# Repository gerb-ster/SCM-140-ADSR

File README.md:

# SCM 140 ADSR

This module is a straight up clone of the ADSR module found it the famous Roland System-100m modular synthesizer from the ’70’s. It consists of 2 identical ADSR generators with a positive and a negative output. I’ve build this some years ago, there are other simpler designs out there, however, it was a really good learning experience.

## Status: Finished

- done: first schematic & board design
- done: breadboard and test
- done: design frontpanel
- done: order PCB and build prototype

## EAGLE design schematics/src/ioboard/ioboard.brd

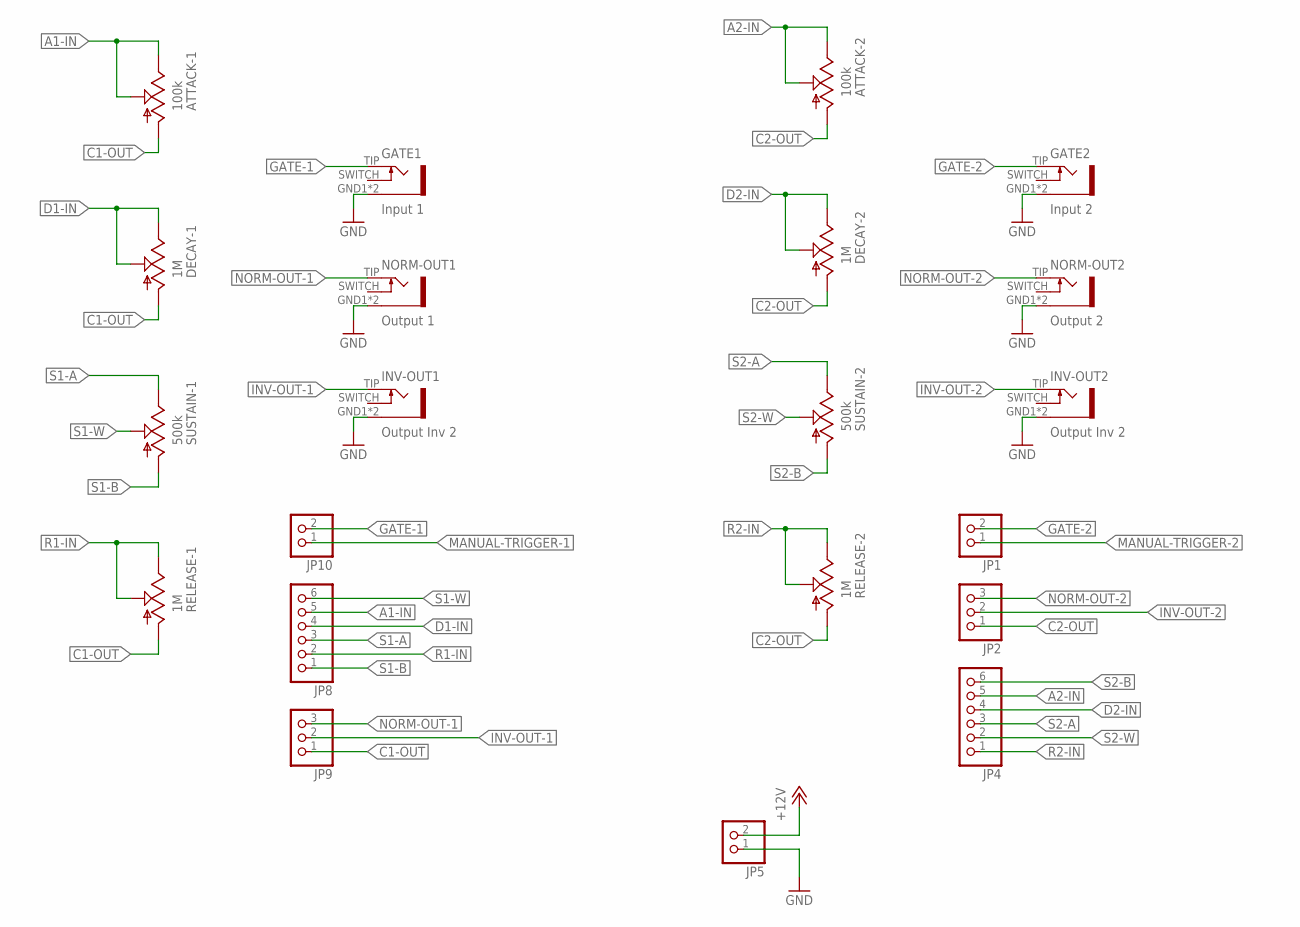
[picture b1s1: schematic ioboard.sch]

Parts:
ATTACK-1, ATTACK-2: 100k; EVUF
DECAY-1, DECAY-2: 1M; EVUF
GATE1: Input 1; PJ301BM
GATE2: Input 2; PJ301BM
INV-OUT1, INV-OUT2: Output Inv 2; PJ301BM
JP1, JP5, JP10: PINHD-1X2; 1X02
JP2, JP9: PINHD-1X3; 1X03
JP4, JP8: PINHD-1X6; 1X06
NORM-OUT1: Output 1; PJ301BM
NORM-OUT2: Output 2; PJ301BM
RELEASE-1, RELEASE-2: 1M; EVUF
SUSTAIN-1, SUSTAIN-2: 500k; EVUF

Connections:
+12V: JP5.2
A1-IN: ATTACK-1.2 (S), ATTACK-1.3 (E), JP8.5
A2-IN: ATTACK-2.2 (S), ATTACK-2.3 (E), JP4.5
C1-OUT: ATTACK-1.1 (A), DECAY-1.1 (A), JP9.1, RELEASE-1.1 (A)
C2-OUT: ATTACK-2.1 (A), DECAY-2.1 (A), JP2.1, RELEASE-2.1 (A)
D1-IN: DECAY-1.2 (S), DECAY-1.3 (E), JP8.4
D2-IN: DECAY-2.2 (S), DECAY-2.3 (E), JP4.4
GATE-1: GATE1.TIP (3), JP10.2
GATE-2: GATE2.TIP (3), JP1.2
GND: GATE1.GND1 (5), GATE1.GND2 (5), GATE2.GND1 (5), GATE2.GND2 (5), INV-OUT1.GND1 (5), INV-OUT1.GND2 (5), INV-OUT2.GND1 (5), INV-OUT2.GND2 (5), JP5.1, NORM-OUT1.GND1 (5), NORM-OUT1.GND2 (5), NORM-OUT2.GND1 (5), NORM-OUT2.GND2 (5)
INV-OUT-1: INV-OUT1.TIP (3), JP9.2
INV-OUT-2: INV-OUT2.TIP (3), JP2.2
MANUAL-TRIGGER-1: JP10.1
MANUAL-TRIGGER-2: JP1.1
NORM-OUT-1: JP9.3, NORM-OUT1.TIP (3)
NORM-OUT-2: JP2.3, NORM-OUT2.TIP (3)
R1-IN: JP8.2, RELEASE-1.2 (S), RELEASE-1.3 (E)
R2-IN: JP4.1, RELEASE-2.2 (S), RELEASE-2.3 (E)
S1-A: JP8.3, SUSTAIN-1.3 (E)
S1-B: JP8.1, SUSTAIN-1.1 (A)
S1-W: JP8.6, SUSTAIN-1.2 (S)
S2-A: JP4.3, SUSTAIN-2.3 (E)
S2-B: JP4.6, SUSTAIN-2.1 (A)
S2-W: JP4.2, SUSTAIN-2.2 (S)

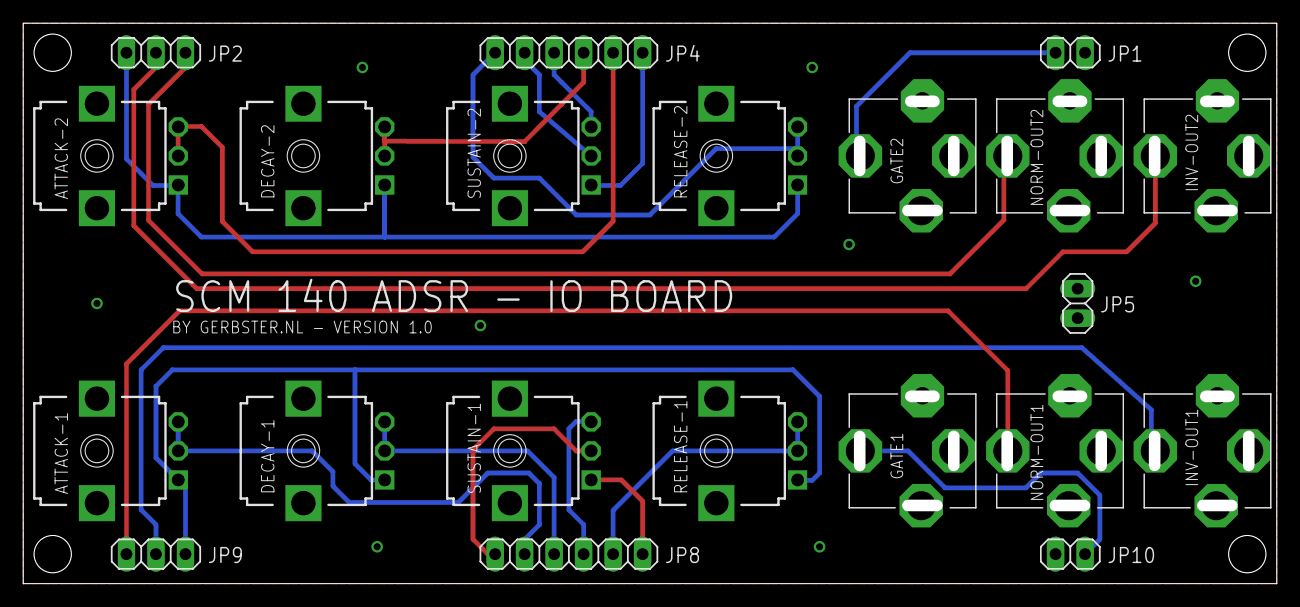
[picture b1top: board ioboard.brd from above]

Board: 2 copper layers, 107.0 x 47.3 mm, 21 parts (0 on the bottom side), 21 nets.

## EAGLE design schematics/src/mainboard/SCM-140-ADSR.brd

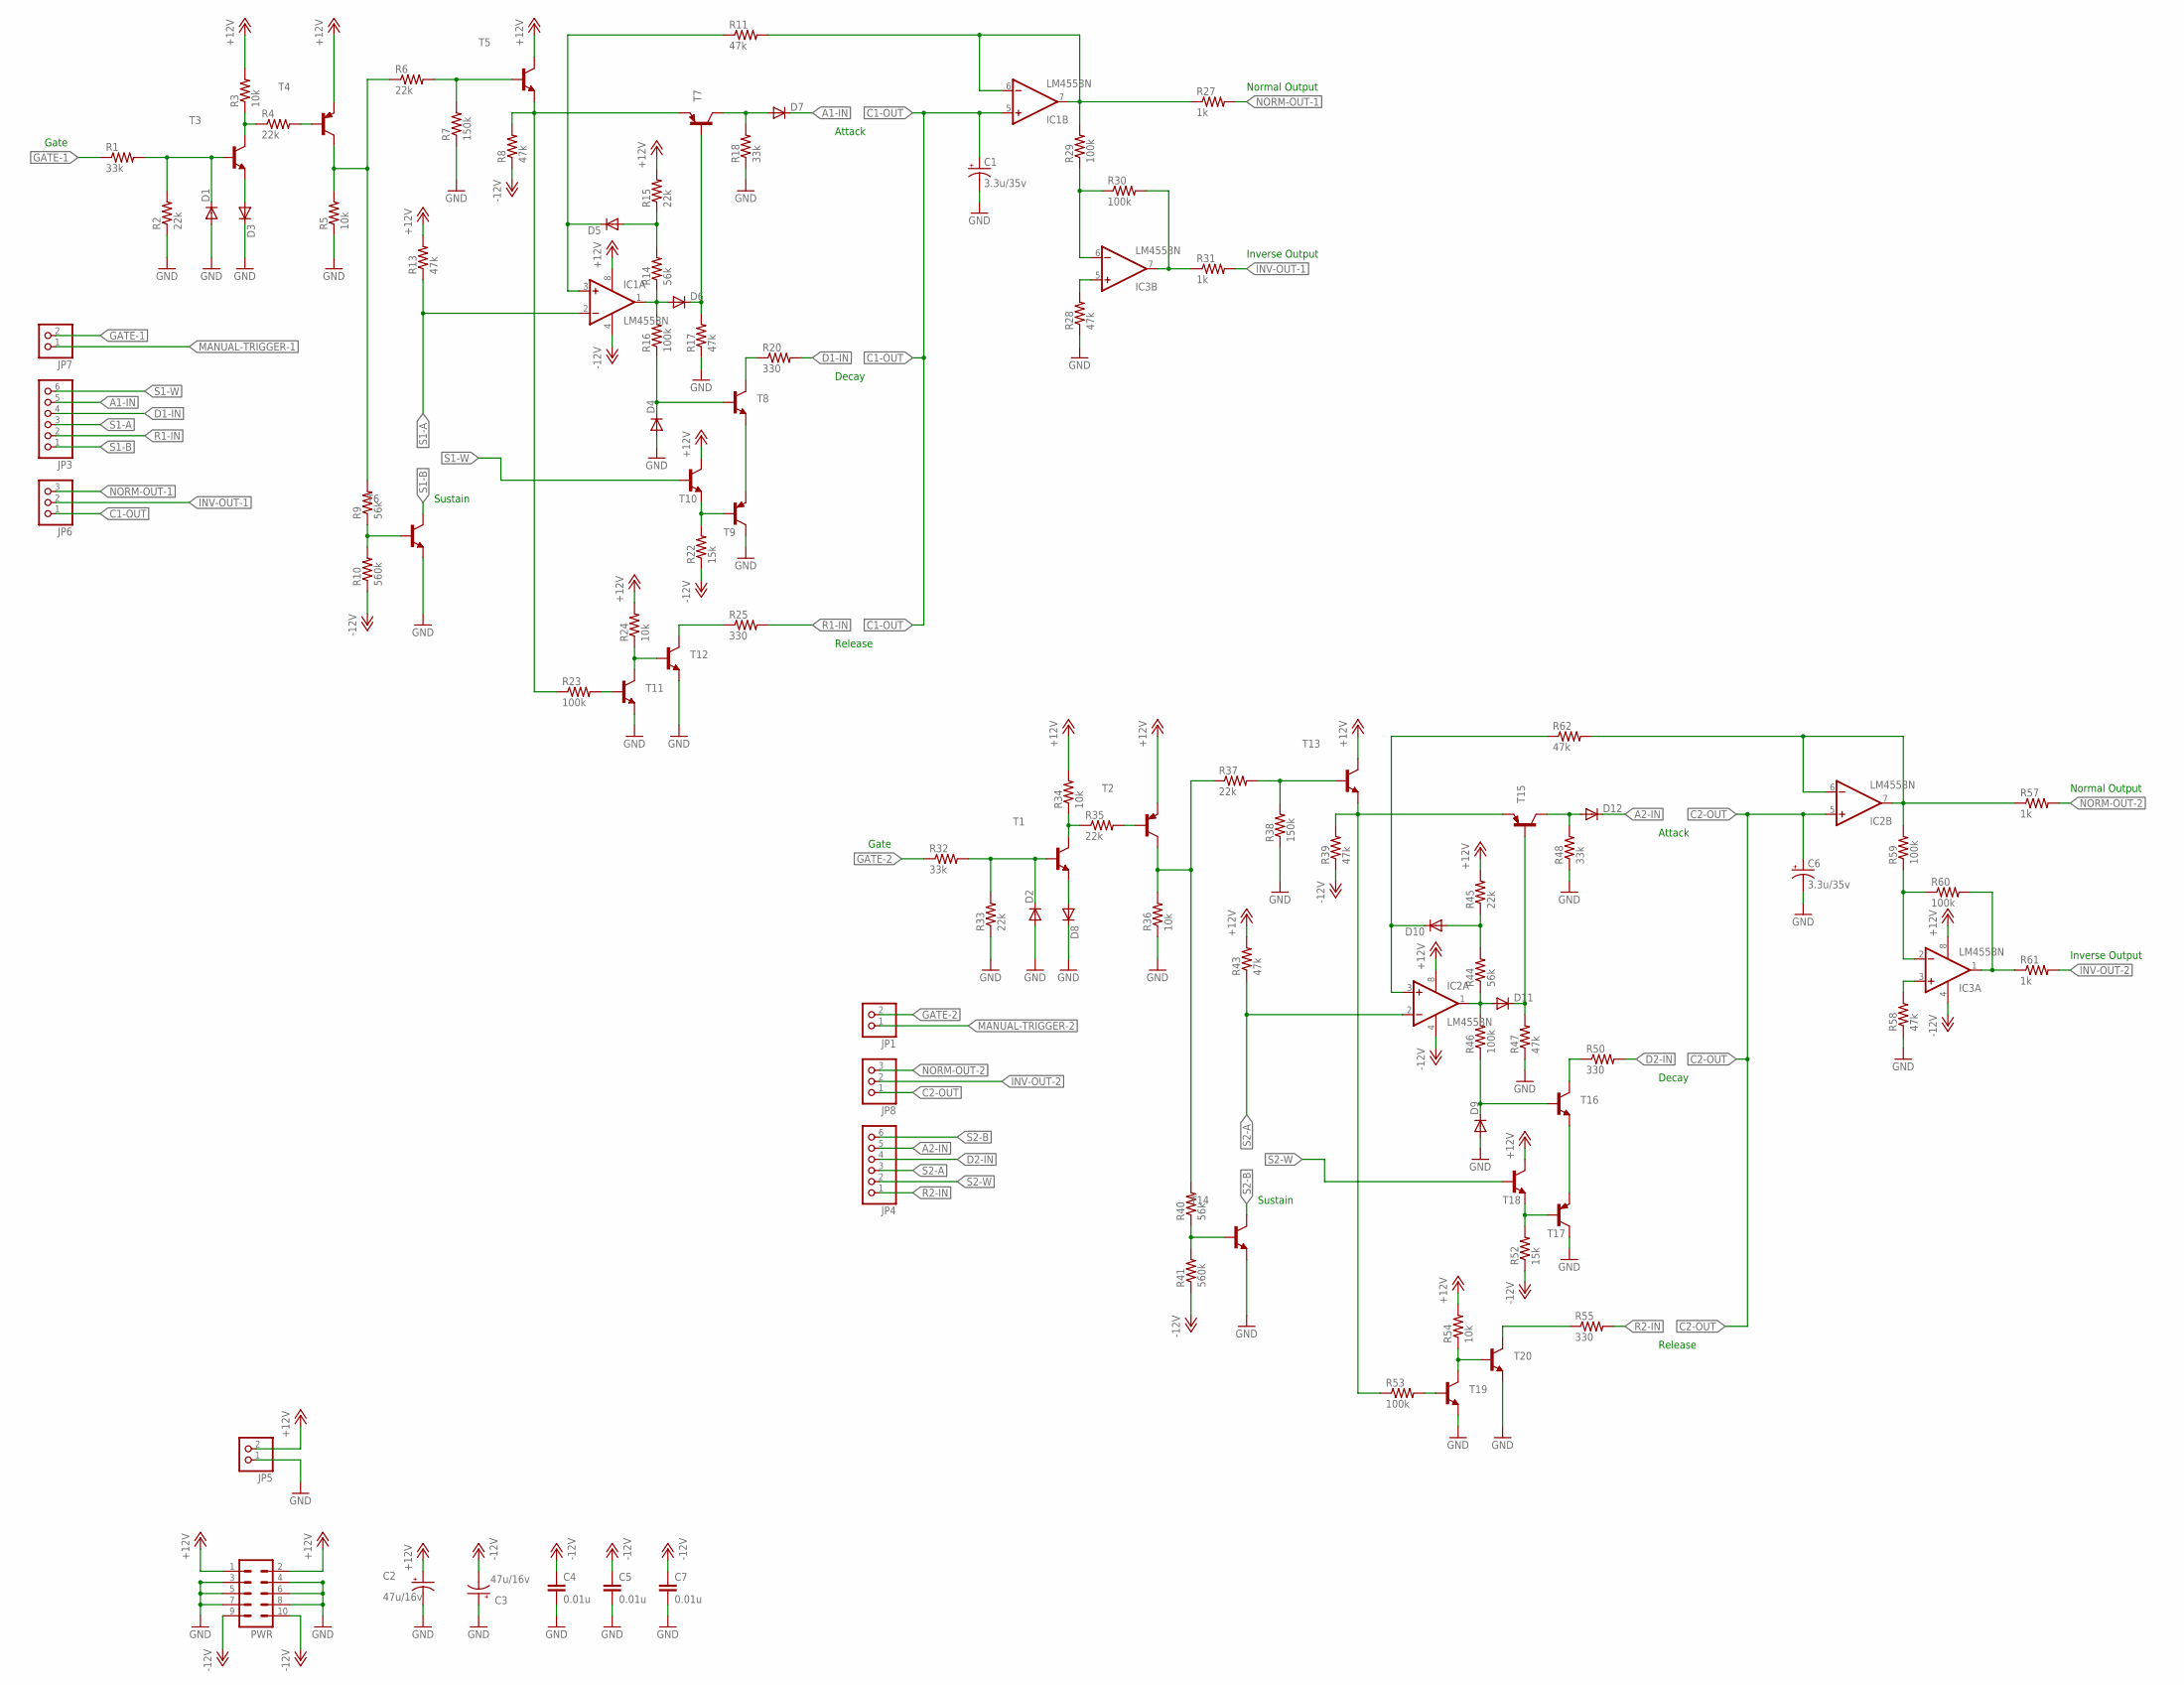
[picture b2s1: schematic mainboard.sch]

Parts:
C1, C6: 3.3u/35v; E2,5-5
C2, C3: 47u/16v; E2,5-5
C4, C5, C7: 0.01u; C025-024X044
D1, D2, D3, D4, D5, D6, D7, D8, D9, D10, D11, D12: 1N4148DO35-7; DO35-7
IC1, IC2, IC3: LM4558N; DIL08
JP1, JP5, JP7: PINHD-1X2; 1X02
JP3, JP4: PINHD-1X6; 1X06
JP6, JP8: PINHD-1X3; 1X03
PWR: ML10
R1, R18, R32, R48: 33k; 0204/7
R2, R4, R6, R15, R33, R35, R37, R45: 22k; 0204/7
R3, R5, R24, R34, R36, R54: 10k; 0204/7
R7, R38: 150k; 0204/7
R8, R11, R13, R17, R28, R39, R43, R47, R58, R62: 47k; 0204/7
R9, R14, R40, R44: 56k; 0204/7
R10, R41: 560k; 0204/7
R16, R23, R29, R30, R46, R53, R59, R60: 100k; 0204/7
R20, R25, R50, R55: 330; 0204/7
R22, R52: 15k; 0204/7
R27, R31, R57, R61: 1k; 0204/7
T1, T3, T5, T6, T8, T10, T11, T12, T13, T14, T16, T18, T19, T20: BC547B-NPN-TO92-CBE; TO92-CBE
T2, T4, T7, T9, T15, T17: BC557B-PNP-TO92-EBC; TO92-EBC

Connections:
+12V: C2.+, IC1.8 (V+), IC2.8 (V+), IC3.8 (V+), JP5.2, PWR.1, PWR.2, R3.2, R13.2, R15.2, R24.2, R34.2, R43.2, R45.2, R54.2, T2.E, T4.E, T5.C, T10.C, T13.C, T18.C
-12V: C3.-, C4.1, C5.1, C7.1, IC1.4 (V-), IC2.4 (V-), IC3.4 (V-), PWR.9, PWR.10, R8.1, R10.1, R22.1, R39.1, R41.1, R52.1
A1-IN: D7.C, JP3.5
A2-IN: D12.C, JP4.5
C1-OUT: C1.+, IC1.5 (+IN), JP6.1
C2-OUT: C6.+, IC2.5 (+IN), JP8.1
D1-IN: JP3.4, R20.2
D2-IN: JP4.4, R50.2
GATE-1: JP7.2, R1.1
GATE-2: JP1.2, R32.1
GND: C1.-, C2.-, C3.+, C4.2, C5.2, C6.-, C7.2, D1.A, D2.A, D3.C, D4.A, D8.C, D9.A, JP5.1, PWR.3, PWR.4, PWR.5, PWR.6, PWR.7, PWR.8, R2.1, R5.1, R7.1, R17.1, R18.1, R28.1, R33.1, R36.1, R38.1, R47.1, R48.1, R58.1, T6.E, T9.C, T11.E, T12.E, T14.E, T17.C, T19.E, T20.E
INV-OUT-1: JP6.2, R31.2
INV-OUT-2: JP8.2, R61.2
MANUAL-TRIGGER-1: D1.C, JP7.1, R1.2, R2.2, T3.B
MANUAL-TRIGGER-2: D2.C, JP1.1, R32.2, R33.2, T1.B
unnamed: D5.C, IC1.3 (+IN), R11.1
unnamed: D3.A, T3.E
unnamed: R3.1, R4.1, T3.C
unnamed: R4.2, T4.B
unnamed: R5.2, R6.1, R9.2, T4.C
unnamed: R8.2, R23.1, T5.E, T7.E
unnamed: R6.2, R7.2, T5.B
unnamed: R9.1, R10.2, T6.B
unnamed: D6.A, IC1.1 (OUT), R14.1, R16.2
unnamed: D4.C, R16.1, T8.B
unnamed: D5.A, R14.2, R15.1
unnamed: IC1.6 (-IN), IC1.7 (OUT), R11.2, R27.1, R29.2
unnamed: D7.A, R18.2, T7.C
unnamed: D6.C, R17.2, T7.B
unnamed: IC3.6 (-IN), R29.1, R30.1
unnamed: R20.1, T8.C
unnamed: R22.2, T9.B, T10.E
unnamed: T8.E, T9.E
unnamed: R23.2, T11.B
unnamed: R24.1, T11.C, T12.B
unnamed: R25.1, T12.C
unnamed: IC3.7 (OUT), R30.2, R31.1
unnamed: D8.A, T1.E
unnamed: IC3.5 (+IN), R28.2
unnamed: R34.1, R35.1, T1.C
unnamed: R35.2, T2.B
unnamed: R36.2, R37.1, R40.2, T2.C
unnamed: R39.2, R53.1, T13.E, T15.E
unnamed: R37.2, R38.2, T13.B
unnamed: R40.1, R41.2, T14.B
unnamed: D11.A, IC2.1 (OUT), R44.1, R46.2
unnamed: D9.C, R46.1, T16.B
unnamed: D10.A, R44.2, R45.1
unnamed: IC2.6 (-IN), IC2.7 (OUT), R57.1, R59.2, R62.2
unnamed: D11.C, R47.2, T15.B
unnamed: D12.A, R48.2, T15.C
unnamed: R50.1, T16.C
unnamed: R52.2, T17.B, T18.E
unnamed: T16.E, T17.E
unnamed: R53.2, T19.B
unnamed: R54.1, T19.C, T20.B
unnamed: R55.1, T20.C
unnamed: IC3.2 (-IN), R59.1, R60.1
unnamed: IC3.1 (OUT), R60.2, R61.1
unnamed: IC3.3 (+IN), R58.2
unnamed: D10.C, IC2.3 (+IN), R62.1
NORM-OUT-1: JP6.3, R27.2
NORM-OUT-2: JP8.3, R57.2
R1-IN: JP3.2, R25.2
R2-IN: JP4.1, R55.2
S1-A: IC1.2 (-IN), JP3.3, R13.1
S1-B: JP3.1, T6.C
S1-W: JP3.6, T10.B
S2-A: IC2.2 (-IN), JP4.3, R43.1
S2-B: JP4.6, T14.C
S2-W: JP4.2, T18.B

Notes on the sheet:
Attack
Decay
Release
Sustain
Gate
Normal Output
Inverse Output

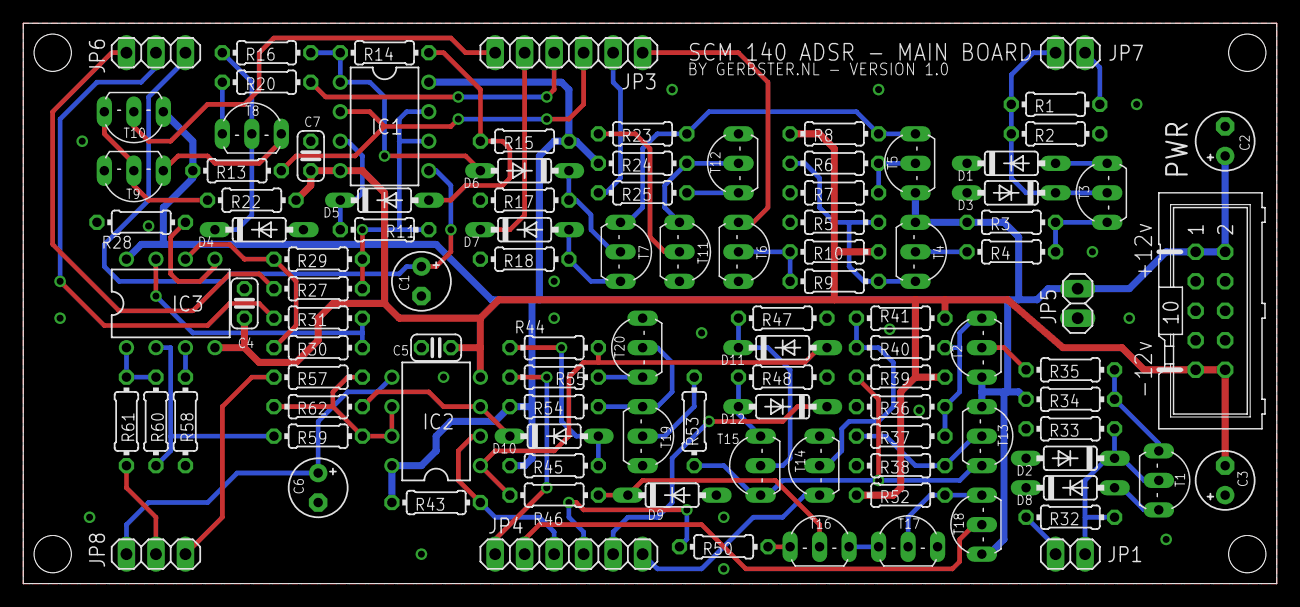
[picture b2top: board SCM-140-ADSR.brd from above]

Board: 2 copper layers, 108.0 x 48.3 mm, 104 parts (0 on the bottom side), 71 nets.

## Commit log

2021-05-06 some files
2021-05-07 Added files & structure
2021-05-10 Added Status
2021-05-11 Added Status & Images
2021-08-06 Updated some schematics and docs
2021-08-10 Fixed some bugs and updated documentation
2022-04-20 Some updates & bugfixes
2022-04-22 Fixed schematics & descriptions
2022-05-17 Updated Firmware
2022-05-18 Updated Faceplates
2022-05-18 Fixed issues
2022-05-21 Fixed schematics
2022-05-28 General updates
